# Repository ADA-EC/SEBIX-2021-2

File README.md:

<h1 align="center"> SEBIX-2021 | Grupo 2</h1>

#### Desenvolvido em 2021 por Gabriel Sotto, Lucas Witzel, Carlos Nery e Marcos Patrício.

## Resumo do Projeto

O projeto SEBIX trata-se do primeiro projeto desenvolvido pelos novos membros do grupo para desenvolver as habilidades individuais e coletivas, preparando-os para os próximos projetos desenvolvidos na ADA. Para o ano de 2021, deveria ser recriado o jogo T-Rex Running em um "gameboy", prototipando o circuito digitalmente em um Arduino e modelando a carcaça em 3D.

<hr />

## 1. Protótipo

Foi pensado inicialmente um único botão para que o dinossauro pule e, para desviar dos pterodáticlos, bastaria apenas não pular. Utilizando o <a href="https://www.tinkercad.com/dashboard">Tikercad</a> para prototipar o circuito, foram utilizados os seguintes materiais:

- 1 Arduino UNO;
- 1 Display LCD 16x2;
- 1 interruptor deslizante;
- 1 Protoboard;
- 1 Botão;
- 2 Resistores de 1K&Omega;
- 1 Buzzer;

Você pode acessar o protótipo <a href="https://www.tinkercad.com/things/aBuyB667oZ1-projeto-sebix-2021-grupo-2/editel?sharecode=ph_fwuVlIoaRs9A8ReaDCT7rvYecoMuUgHqlTlmYOHI">Clicando Aqui</a>.

<hr />

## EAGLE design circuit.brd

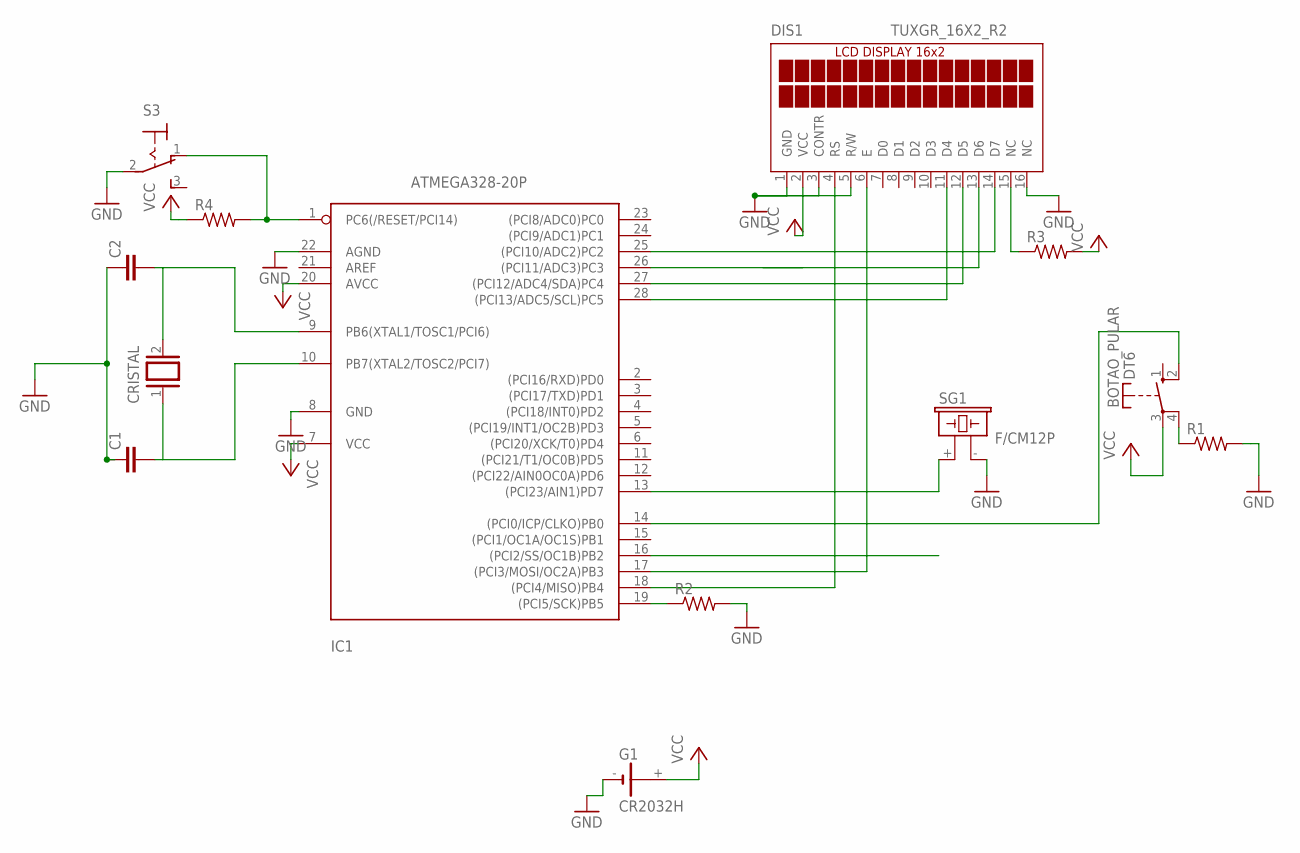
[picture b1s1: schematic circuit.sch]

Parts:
BOTAO_PULAR: DT6
C1, C2: C5/3.5; C5B3.5
CRISTAL: XTAL/S; QS
DIS1: TUXGR_16X2_R2
G1: CR2032H
IC1: ATMEGA328-20P; DIL28-3
R1, R2, R3, R4: R-US_0204/7; 0204/7
S3: 320-916
SG1: F/CM12P

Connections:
GND: C1.1, C2.1, DIS1.1 (GND), DIS1.3 (CONTR), DIS1.5 (R/W), DIS1.16 (NC), G1.-, IC1.8 (GND), IC1.22 (AGND), R1.2, R2.2, S3.2, SG1.- (2)
unnamed: IC1.13 ((PCI23/AIN1)PD7), SG1.+ (1)
unnamed: IC1.19 ((PCI5/SCK)PB5), R2.1
unnamed: DIS1.15 (NC), R3.1
unnamed: IC1.1 (PC6(/RESET/PCI14)), R4.2, S3.1 (O)
unnamed: C1.2, CRISTAL.1, IC1.10 (PB7(XTAL2/TOSC2/PCI7))
unnamed: C2.2, CRISTAL.2, IC1.9 (PB6(XTAL1/TOSC1/PCI6))
unnamed: DIS1.4 (RS), IC1.18 ((PCI4/MISO)PB4)
unnamed: DIS1.6 (E), IC1.17 ((PCI3/MOSI/OC2A)PB3)
unnamed: DIS1.11 (D4), IC1.28 ((PCI13/ADC5/SCL)PC5)
unnamed: DIS1.12 (D5), IC1.27 ((PCI12/ADC4/SDA)PC4)
unnamed: DIS1.13 (D6), IC1.26 ((PCI11/ADC3)PC3)
unnamed: DIS1.14 (D7), IC1.25 ((PCI10/ADC2)PC2)
unnamed: BOTAO_PULAR.4, R1.1
unnamed: BOTAO_PULAR.2 (S), IC1.14 ((PCI0/ICP/CLKO)PB0)
VCC: BOTAO_PULAR.3, DIS1.2 (VCC), G1.+, IC1.7 (VCC), IC1.20 (AVCC), R3.2, R4.1

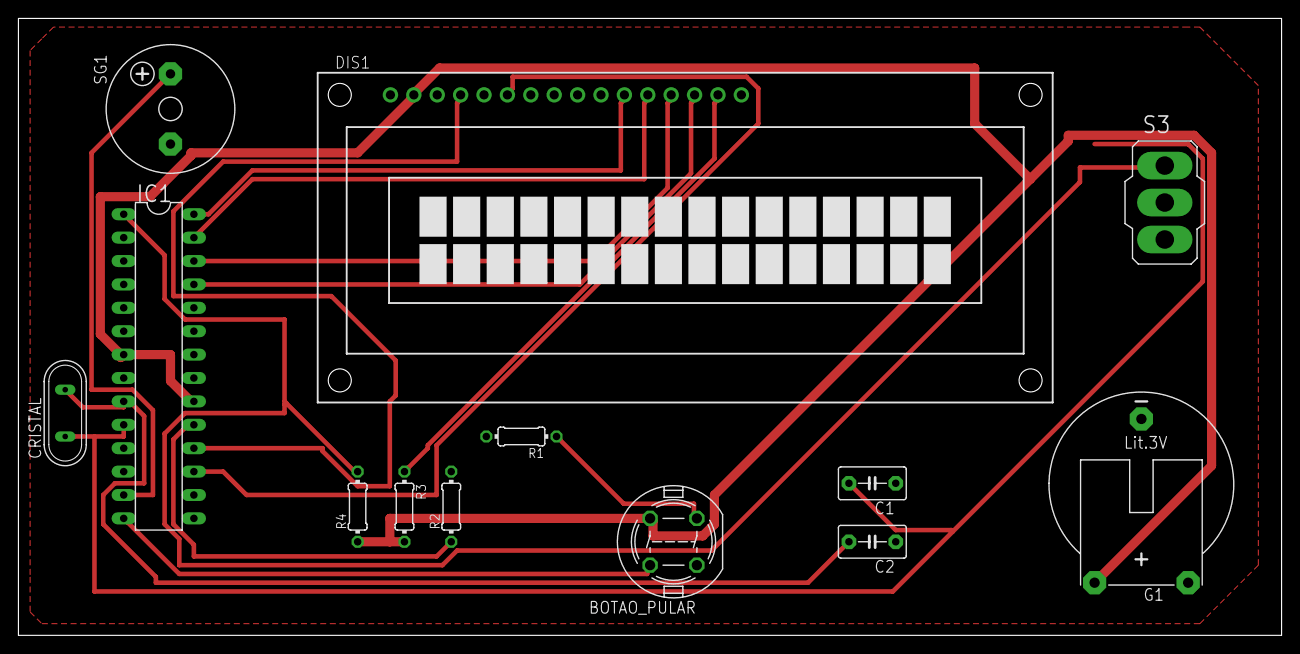
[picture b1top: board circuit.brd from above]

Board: 2 copper layers, 137.1 x 67.0 mm, 13 parts (0 on the bottom side), 16 nets.

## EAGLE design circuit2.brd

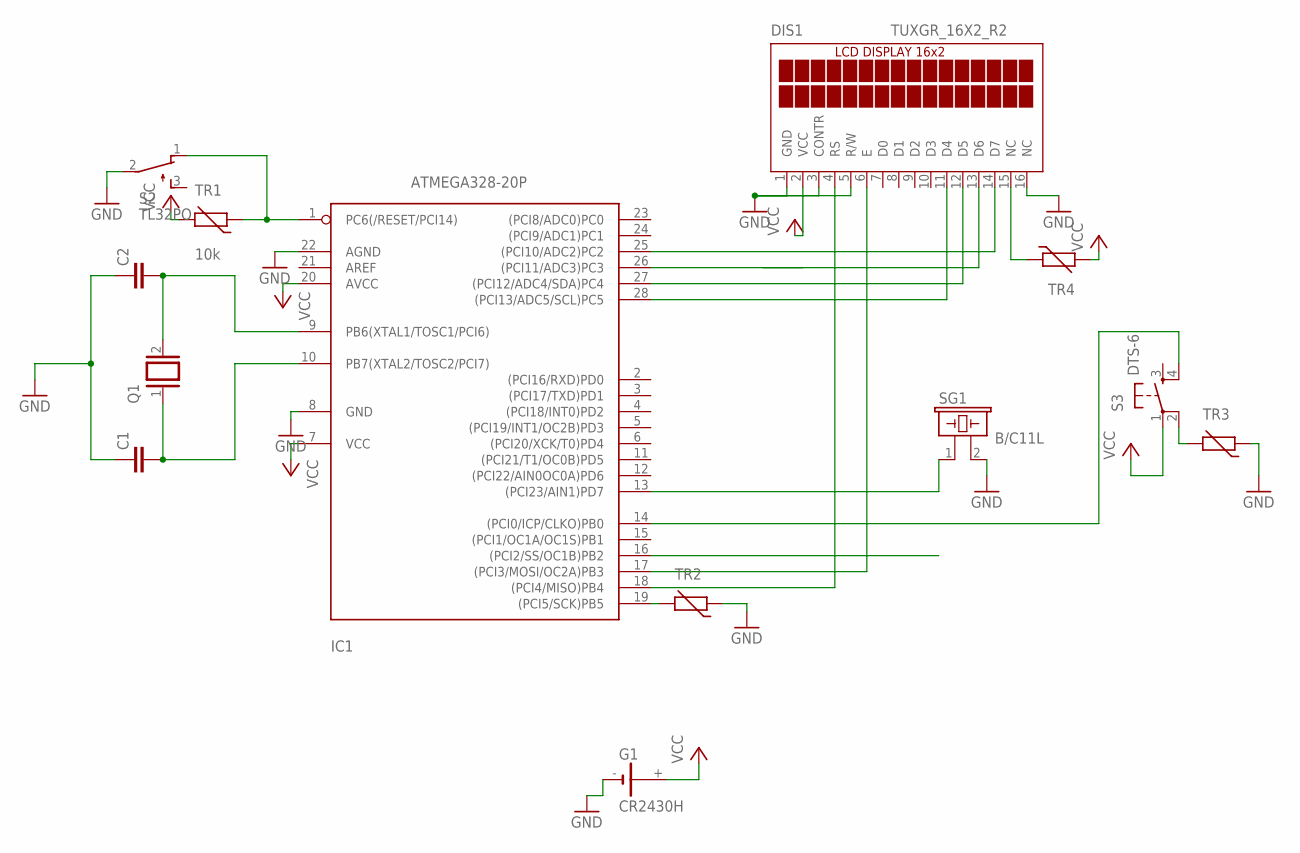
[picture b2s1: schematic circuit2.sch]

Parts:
C1, C2: C2.5/2; C2.5-2
DIS1: TUXGR_16X2_R2
G1: CR2430H
IC1: ATMEGA328-20P; DIL28-3
Q1: XTAL/S; QS
S2: TL32PO; TL3XPO
S3: DTS-6
SG1: B/C11L
TR1: 10k; R-5
TR2, TR3, TR4: THERMISTOR_R-5; R-5

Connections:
GND: C1.1, C2.1, DIS1.1 (GND), DIS1.3 (CONTR), DIS1.5 (R/W), DIS1.16 (NC), G1.-, IC1.8 (GND), IC1.22 (AGND), S2.2, SG1.2, TR2.1, TR3.1
unnamed: IC1.13 ((PCI23/AIN1)PD7), SG1.1
unnamed: IC1.1 (PC6(/RESET/PCI14)), S2.1 (O), TR1.1
unnamed: C1.2, IC1.10 (PB7(XTAL2/TOSC2/PCI7)), Q1.1
unnamed: C2.2, IC1.9 (PB6(XTAL1/TOSC1/PCI6)), Q1.2
unnamed: IC1.19 ((PCI5/SCK)PB5), TR2.2
unnamed: DIS1.15 (NC), TR4.1
unnamed: DIS1.4 (RS), IC1.18 ((PCI4/MISO)PB4)
unnamed: DIS1.6 (E), IC1.17 ((PCI3/MOSI/OC2A)PB3)
unnamed: DIS1.11 (D4), IC1.28 ((PCI13/ADC5/SCL)PC5)
unnamed: DIS1.12 (D5), IC1.27 ((PCI12/ADC4/SDA)PC4)
unnamed: DIS1.13 (D6), IC1.26 ((PCI11/ADC3)PC3)
unnamed: DIS1.14 (D7), IC1.25 ((PCI10/ADC2)PC2)
unnamed: S3.2, TR3.2
unnamed: IC1.14 ((PCI0/ICP/CLKO)PB0), S3.4
VCC: DIS1.2 (VCC), G1.+, IC1.7 (VCC), IC1.20 (AVCC), S3.1, TR1.2, TR4.2

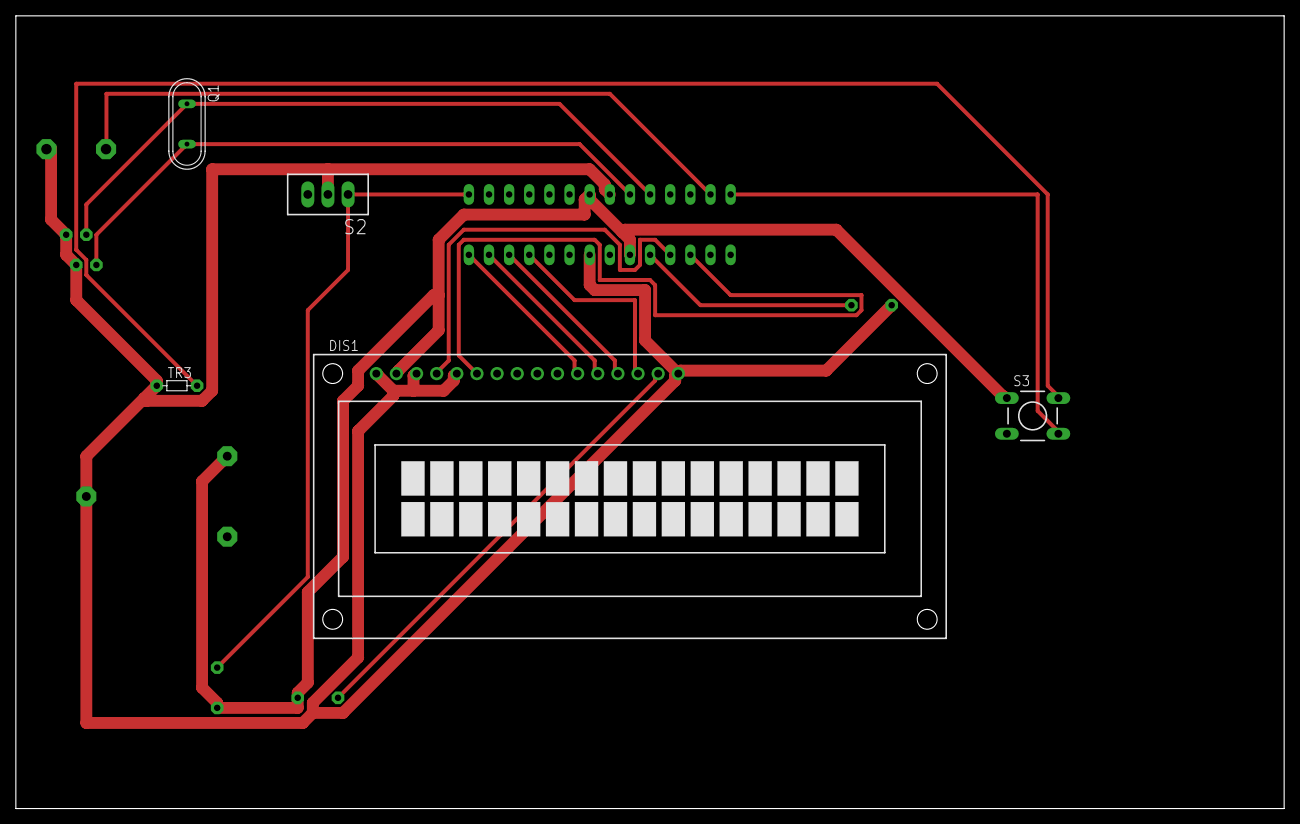
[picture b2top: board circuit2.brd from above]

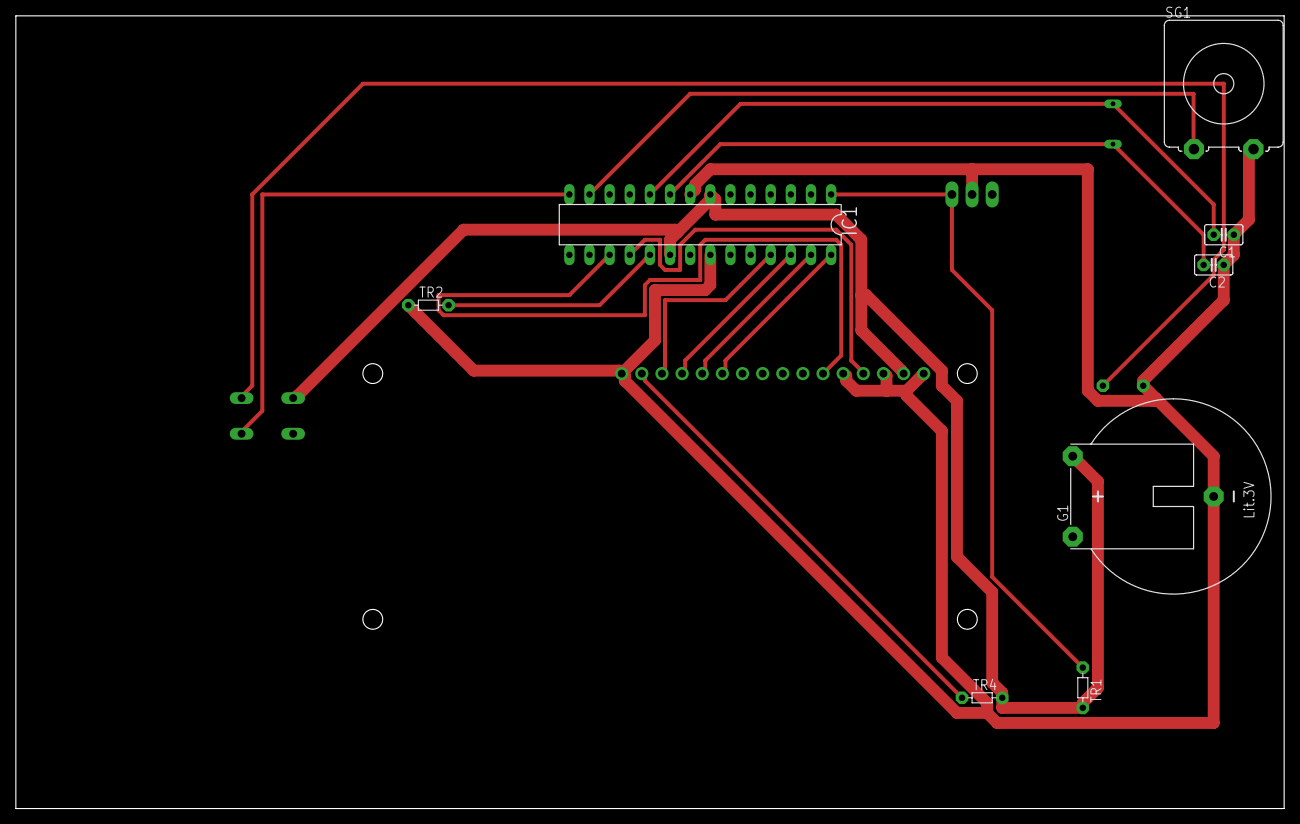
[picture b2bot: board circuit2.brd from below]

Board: 2 copper layers, 160.0 x 100.0 mm, 13 parts (8 on the bottom side), 16 nets.

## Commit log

2021-10-09 Atualização do README
    Foram incluídas todas as coisas feitas no projeto até então, isto é, uma descrição do que será o SEBIX e o protótipo do circuito desenvolvido.
2021-10-09 Correções no README
    Alguns erros de digitação foram encontrados e corrigidos
2021-10-10 [README] Atualização do circuito
    Alteração da imagem do circuito e do link de acesso a ele.
2022-03-10 Adição dos modelos 3D dos principais componentes
2022-03-12 Atualização das trilhas com os modelos 3D
2022-03-12 Versão final do circuito
